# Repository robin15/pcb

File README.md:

# KM54ALC

## image

<br><br><br>

# kmykbd_l
## image

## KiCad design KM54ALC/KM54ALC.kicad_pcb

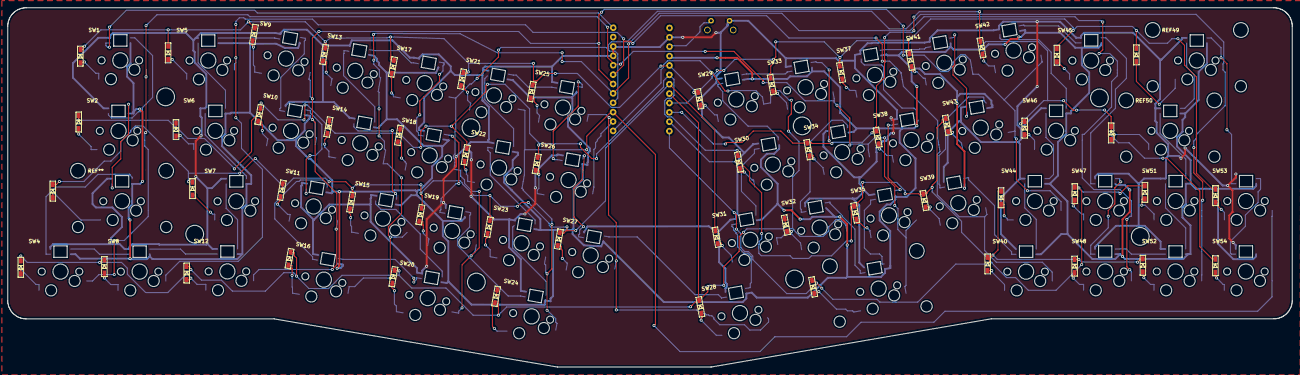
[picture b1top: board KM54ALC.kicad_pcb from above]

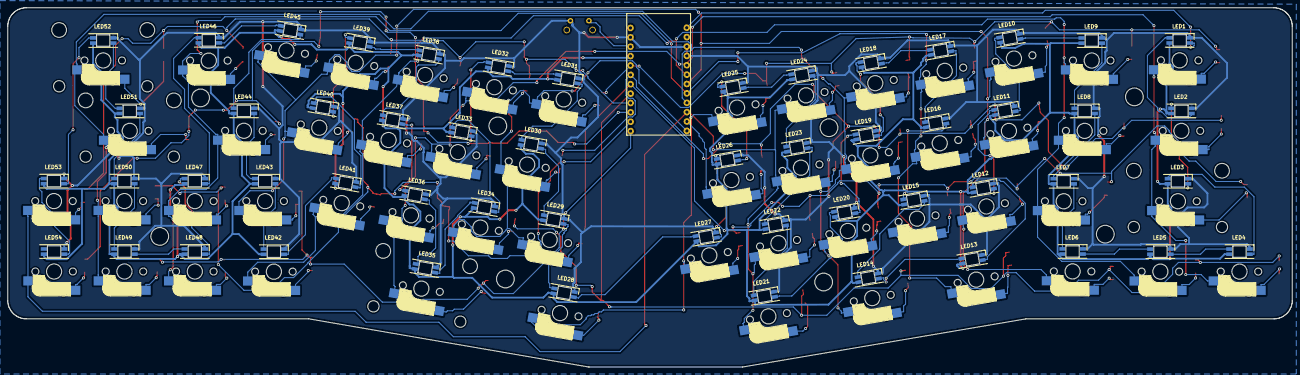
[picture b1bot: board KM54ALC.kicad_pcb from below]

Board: 2 copper layers, 347.8 x 97.3 mm, 172 parts (54 on the bottom side), 127 nets.

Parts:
D1, D2, D3, D4, D5, D6, D7, D8, D9, D10, D11, D12, D13, D14, D15, D16, D17, D18, D19, D20, D21, D22, D23, D24, D25, D26, D27, D28, D29, D30, D31, D32, D33, D34, D35, D36, D37, D38, D39, D40, D41, D42, D43, D44, D45, D46, D47, D48, D49, D50, D51, D52, D53, D54: D; D3_SMD_v2
LED1, LED2, LED3, LED4, LED5, LED6, LED7, LED8, LED9, LED10, LED11, LED12, LED13, LED14, LED15, LED16, LED17, LED18, LED19, LED20, LED21, LED22, LED23, LED24, LED25, LED26, LED27, LED28, LED29, LED30, LED31, LED32, LED33, LED34, LED35, LED36, LED37, LED38, LED39, LED40, LED41, LED42, LED43, LED44, LED45, LED46, LED47, LED48, LED49, LED50, LED51, LED52, LED53, LED54: YS-SK6812MINI-E
Ref01, Ref02, Ref03, Ref03#2, Ref04, Ref04#2, Ref05, Ref06: Val**; M2_HOLE_v2
SW1, SW2, SW4, SW5, SW6, SW7, SW8, SW9, SW10, SW11, SW12, SW13, SW14, SW15, SW16, SW17, SW18, SW19, SW20, SW21, SW22, SW23, SW24, SW25, SW26, SW27, SW28, SW29, SW30, SW31, SW32, SW33, SW34, SW35, SW37, SW38, SW39, SW40, SW41, SW42, SW43, SW44, SW45, SW46, SW47, SW48, SW51, SW52, SW53, SW54: SW_PUSH; CherryMX_Hotswap
SW3, SW36, SW49, SW50: SW_PUSH; 2U-Stabilizer
SW57: SW_Push; tact_switch2
U1: ProMicro; ProMicro-Flip

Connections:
GND: LED1.3, LED2.3, LED3.3, LED4.3, LED5.3, LED6.3, LED7.3, LED8.3, LED9.3, LED10.3, LED11.3, LED12.3, LED13.3, LED14.3, LED15.3, LED16.3, LED17.3, LED18.3, LED19.3, LED20.3, LED21.3, LED22.3, LED23.3, LED24.3, LED25.3, LED26.3, LED27.3, LED28.3, LED29.3, LED30.3, LED31.3, LED32.3, LED33.3, LED34.3, LED35.3, LED36.3, LED37.3, LED38.3, LED39.3, LED40.3, LED41.3, LED42.3, LED43.3, LED44.3, LED45.3, LED46.3, LED47.3, LED48.3, LED49.3, LED50.3, LED51.3, LED52.3, LED53.3, LED54.3, SW57.2, U1.3, U1.4, U1.23
LED: LED1.4, U1.1
unnamed: D1.2, SW1.2
unnamed: D2.2, SW2.2
unnamed: D3.2, SW3.2
unnamed: D4.2, SW4.2
unnamed: D5.2, SW5.2
unnamed: D6.2, SW6.2
unnamed: D7.2, SW7.2
unnamed: D8.2, SW8.2
unnamed: D9.2, SW9.2
unnamed: D10.2, SW10.2
unnamed: D11.2, SW11.2
unnamed: D12.2, SW12.2
unnamed: D13.2, SW13.2
unnamed: D14.2, SW14.2
unnamed: D15.2, SW15.2
unnamed: D16.2, SW16.2
unnamed: D17.2, SW17.2
unnamed: D18.2, SW18.2
unnamed: D19.2, SW19.2
unnamed: D20.2, SW20.2
unnamed: D21.2, SW21.2
unnamed: D22.2, SW22.2
unnamed: D23.2, SW23.2
unnamed: D24.2, SW24.2
unnamed: D25.2, SW25.2
unnamed: D26.2, SW26.2
unnamed: D27.2, SW27.2
unnamed: D28.2, SW28.2
unnamed: D29.2, SW29.2
unnamed: D30.2, SW30.2
unnamed: D31.2, SW31.2
unnamed: D32.2, SW32.2
unnamed: D33.2, SW33.2
unnamed: D34.2, SW34.2
unnamed: D35.2, SW35.2
unnamed: D36.2, SW36.2
unnamed: D37.2, SW37.2
unnamed: D38.2, SW38.2
unnamed: D39.2, SW39.2
unnamed: D40.2, SW40.2
unnamed: D41.2, SW41.2
unnamed: D42.2, SW42.2
unnamed: D43.2, SW43.2
unnamed: D44.2, SW44.2
unnamed: D45.2, SW45.2
unnamed: D46.2, SW46.2
unnamed: D47.2, SW47.2
unnamed: D48.2, SW48.2
unnamed: D49.2, SW49.2
unnamed: D50.2, SW50.2
unnamed: D51.2, SW51.2
unnamed: D52.2, SW52.2
unnamed: D53.2, SW53.2
unnamed: D54.2, SW54.2
unnamed: LED1.2, LED2.4
unnamed: LED2.2, LED3.4
unnamed: LED3.2, LED4.4
unnamed: LED4.2, LED5.4
unnamed: LED5.2, LED6.4
unnamed: LED6.2, LED7.4
unnamed: LED7.2, LED8.4
unnamed: LED8.2, LED9.4
unnamed: LED10.2, LED11.4
unnamed: LED9.2, LED10.4
unnamed: LED11.2, LED12.4
unnamed: LED12.2, LED13.4
unnamed: LED13.2, LED14.4
unnamed: LED14.2, LED15.4
unnamed: LED15.2, LED16.4
unnamed: LED16.2, LED17.4
unnamed: LED17.2, LED18.4
unnamed: LED18.2, LED19.4
unnamed: LED19.2, LED20.4
unnamed: LED20.2, LED21.4
unnamed: LED21.2, LED22.4
unnamed: LED22.2, LED23.4
unnamed: LED23.2, LED24.4
unnamed: LED24.2, LED25.4
unnamed: LED25.2, LED26.4
unnamed: LED26.2, LED27.4
unnamed: LED27.2, LED28.4
unnamed: LED28.2, LED29.4
unnamed: LED29.2, LED30.4
unnamed: LED30.2, LED31.4
unnamed: LED31.2, LED32.4
unnamed: LED32.2, LED33.4
unnamed: LED33.2, LED34.4
unnamed: LED34.2, LED35.4
unnamed: LED35.2, LED36.4
unnamed: LED36.2, LED37.4
unnamed: LED37.2, LED38.4
unnamed: LED38.2, LED39.4
unnamed: LED39.2, LED40.4
unnamed: LED40.2, LED41.4
unnamed: LED41.2, LED42.4
unnamed: LED42.2, LED43.4
unnamed: LED43.2, LED44.4
unnamed: LED44.2, LED45.4
unnamed: LED45.2, LED46.4
unnamed: LED46.2, LED47.4
unnamed: LED47.2, LED48.4
unnamed: LED48.2, LED49.4
unnamed: LED49.2, LED50.4
unnamed: LED50.2, LED51.4
unnamed: LED51.2, LED52.4
unnamed: LED52.2, LED53.4
unnamed: LED53.2, LED54.4
VCC: LED1.1, LED2.1, LED3.1, LED4.1, LED5.1, LED6.1, LED7.1, LED8.1, LED9.1, LED10.1, LED11.1, LED12.1, LED13.1, LED14.1, LED15.1, LED16.1, LED17.1, LED18.1, LED19.1, LED20.1, LED21.1, LED22.1, LED23.1, LED24.1, LED25.1, LED26.1, LED27.1, LED28.1, LED29.1, LED30.1, LED31.1, LED32.1, LED33.1, LED34.1, LED35.1, LED36.1, LED37.1, LED38.1, LED39.1, LED40.1, LED41.1, LED42.1, LED43.1, LED44.1, LED45.1, LED46.1, LED47.1, LED48.1, LED49.1, LED50.1, LED51.1, LED52.1, LED53.1, LED54.1, U1.21
col0: SW1.1, SW2.1, SW3.1, SW4.1, SW33.1, SW34.1, SW35.1, SW36.1, U1.5
col1: SW5.1, SW6.1, SW7.1, SW8.1, SW37.1, SW38.1, SW39.1, SW40.1, U1.6
col2: SW9.1, SW10.1, SW11.1, SW12.1, SW41.1, SW42.1, SW43.1, SW44.1, U1.7
col3: SW13.1, SW14.1, SW15.1, SW16.1, SW45.1, SW46.1, SW47.1, SW48.1, U1.8
col4: SW17.1, SW18.1, SW19.1, SW20.1, SW49.1, SW50.1, SW51.1, SW52.1, U1.9
col5: SW21.1, SW22.1, SW23.1, SW24.1, SW53.1, SW54.1, U1.10
col6: SW25.1, SW26.1, SW27.1, SW28.1, U1.11
col7: SW29.1, SW30.1, SW31.1, SW32.1, U1.12
row0: D1.1, D5.1, D9.1, D13.1, D17.1, D21.1, D25.1, D29.1, U1.20
row1: D2.1, D6.1, D10.1, D14.1, D18.1, D22.1, D26.1, D30.1, U1.19
row2: D3.1, D7.1, D11.1, D15.1, D19.1, D23.1, D27.1, D31.1, U1.18
row3: D4.1, D8.1, D12.1, D16.1, D20.1, D24.1, D28.1, D32.1, U1.17
row4: D33.1, D37.1, D41.1, D45.1, D49.1, D53.1, U1.16
row5: D34.1, D38.1, D42.1, D46.1, D50.1, D54.1, U1.15
row6: D35.1, D39.1, D43.1, D47.1, D51.1, U1.14
row7: D36.1, D40.1, D44.1, D48.1, D52.1, U1.13
rst: SW57.1, U1.22

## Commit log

2019-04-14 rev.0.1
2019-05-06 add case data
2020-12-29 resize hole size for Conthrough
2020-12-29 modify silk
2020-12-30 remove front LED pattern
2021-01-17 move to new folder
2021-01-17 add pcb data of kmykbd long ver.
2022-02-21 add new design keyboard
2022-02-22 add README
